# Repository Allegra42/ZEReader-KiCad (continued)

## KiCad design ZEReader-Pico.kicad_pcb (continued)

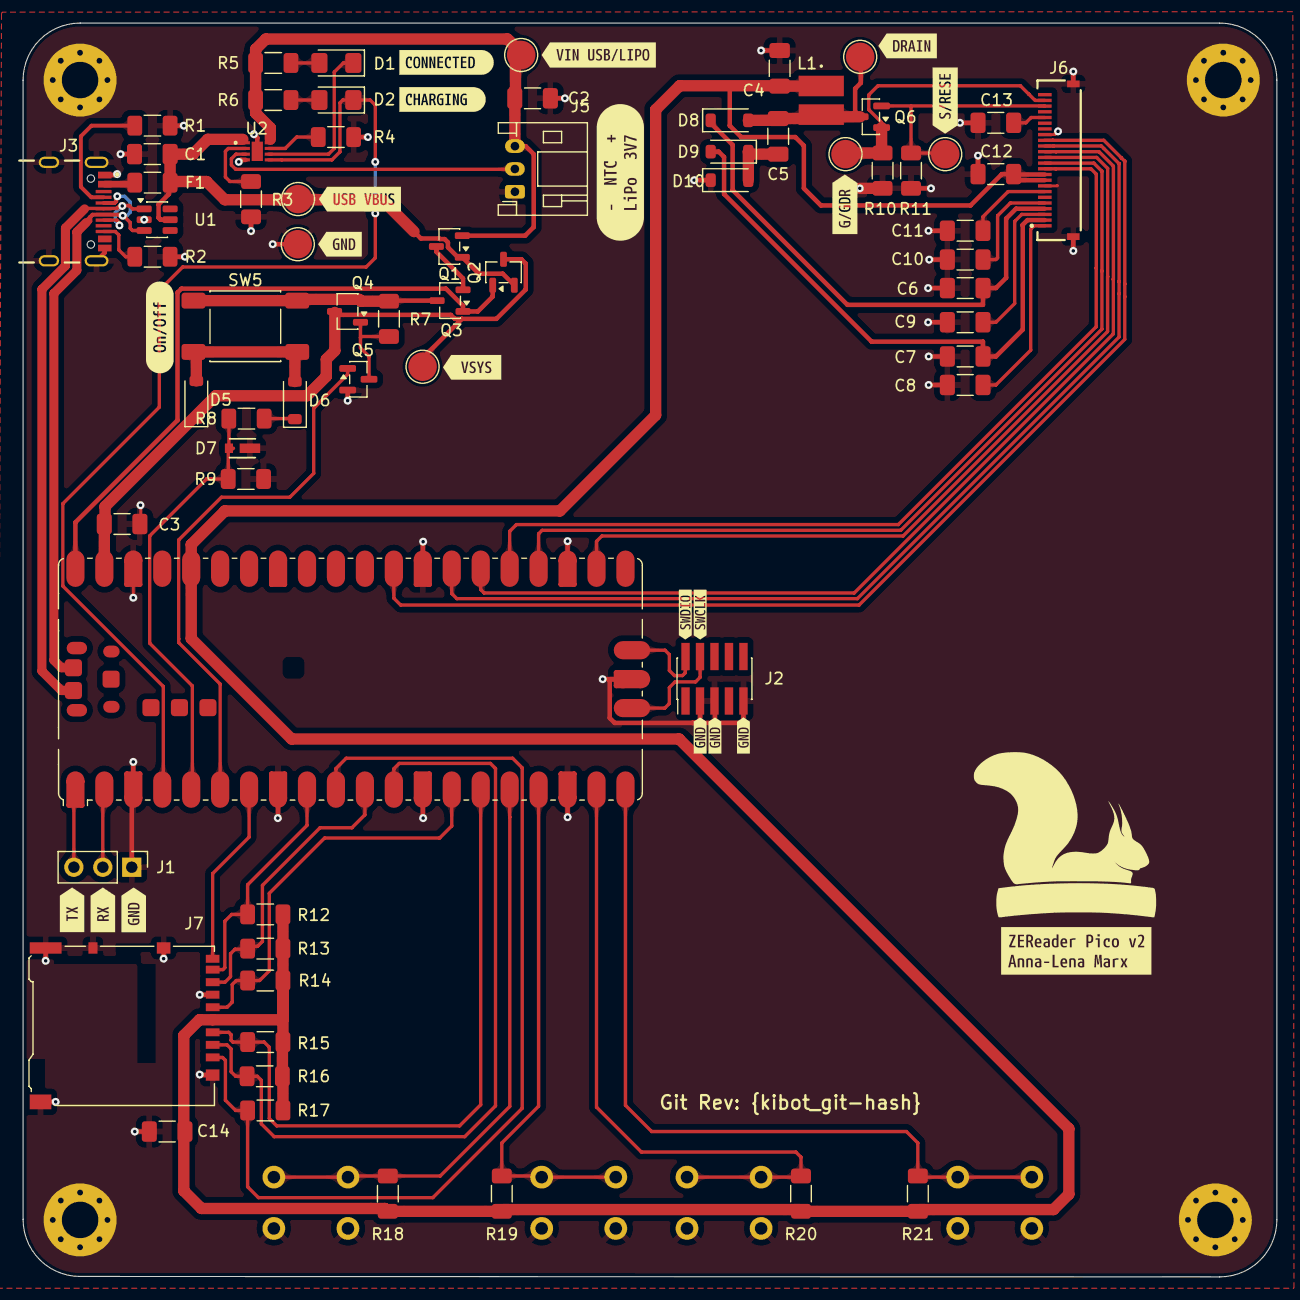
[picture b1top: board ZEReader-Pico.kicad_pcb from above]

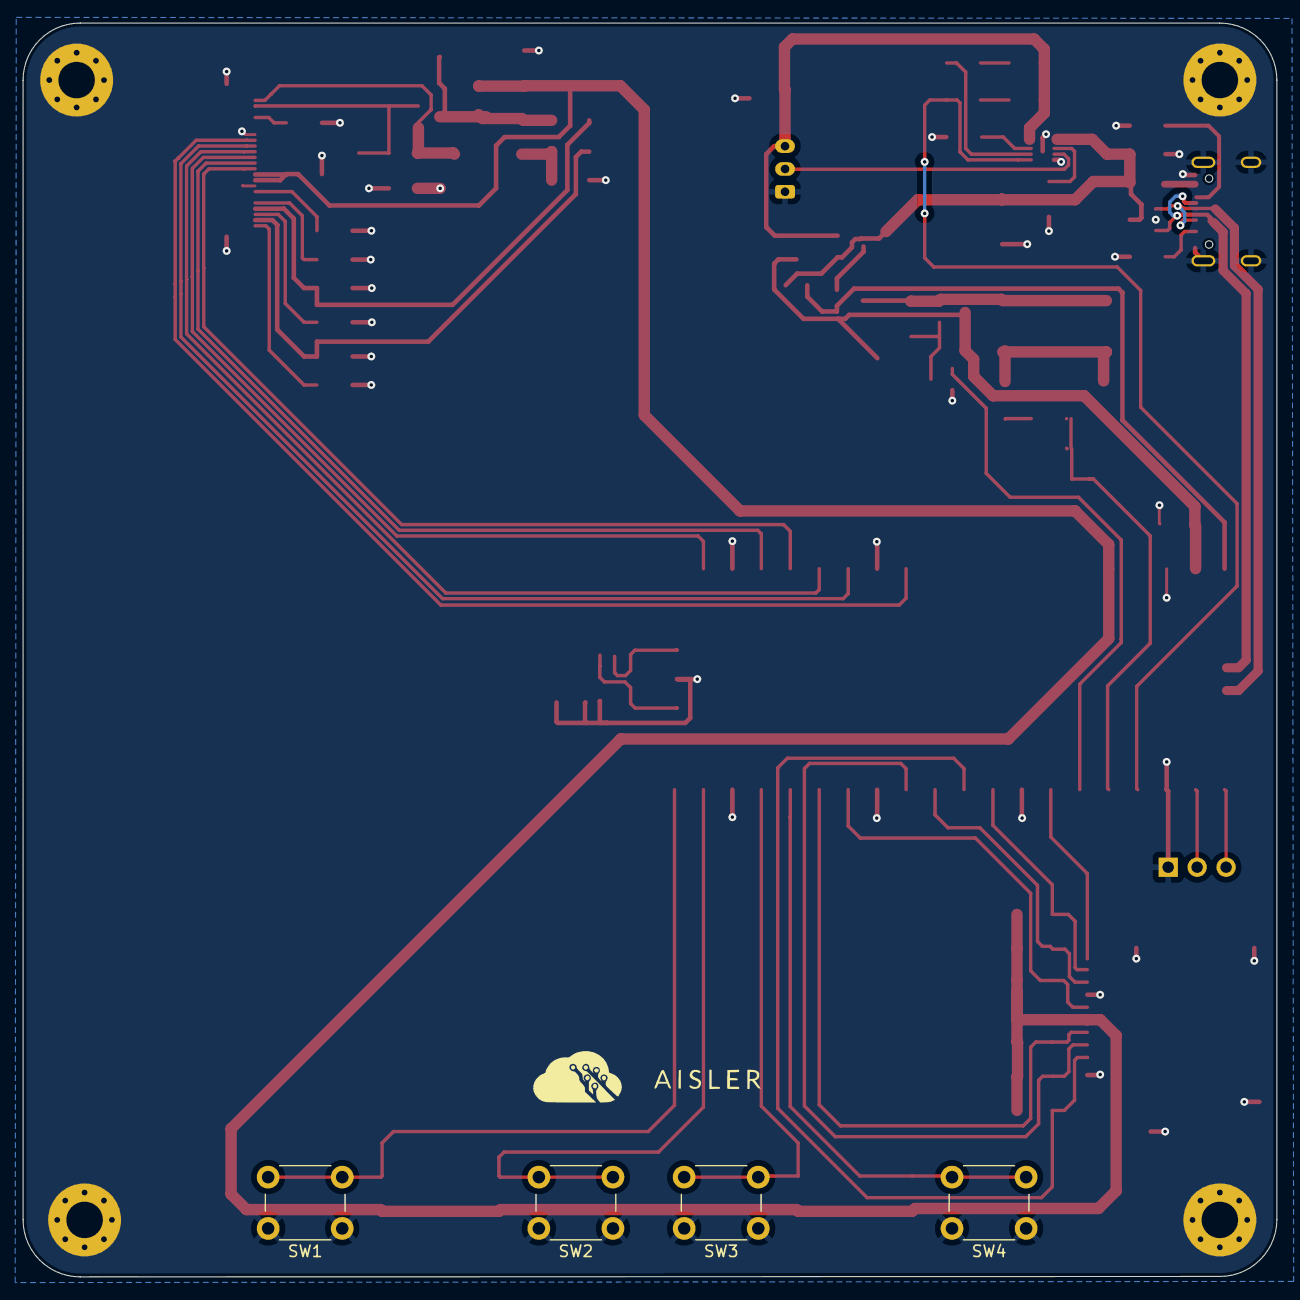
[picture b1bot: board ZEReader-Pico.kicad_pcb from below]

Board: 2 copper layers, 110.0 x 110.0 mm, 96 parts (4 on the bottom side), 57 nets.

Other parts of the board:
kibuzzard-1: G***; kibuzzard-6910EAB5
kibuzzard-2: G***; kibuzzard-6910F1E0
kibuzzard-3: G***; kibuzzard-6910EA92
kibuzzard-4: G***; kibuzzard-6910F073
kibuzzard-5: G***; kibuzzard-6910F03B
kibuzzard-6: G***; kibuzzard-6910EACE
kibuzzard-7: G***; kibuzzard-6910EA89
kibuzzard-8: G***; kibuzzard-6910EAAC
kibuzzard-10: G***; kibuzzard-6910EB09
kibuzzard-14: G***; kibuzzard-6910EC15
kibuzzard-15: G***; kibuzzard-6910EC3B
kibuzzard-16: G***; kibuzzard-6910EC48
kibuzzard-17: G***; kibuzzard-6910ECBF
kibuzzard-691E57BD: G***; kibuzzard-691E57BD
kibuzzard-691E5833: G***; kibuzzard-691E5833
kibuzzard-691EE38D: G***; kibuzzard-691EE38D
kibuzzard-691EE385: G***; kibuzzard-691EE385
kibuzzard-691EE480: G***; kibuzzard-691EE480
kibuzzard-691EE489: G***; kibuzzard-691EE489
kibuzzard-691EE495: G***; kibuzzard-691EE495

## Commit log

2025-01-26 Create inital KiCad hierarchical schematics structure
2025-01-27 Adds SD card connector, control buttons and debug headers
2025-01-27 Add EPD Driver Circuit
2025-01-29 Added USB-C, Battery Charging andOn/Off
2025-01-30 Added some more notes, testpoints and rechecked footprints and parts
2025-01-31 Changed buttons to smaller ones, updated some comments
2025-02-03 Added CC line pulldown resistors
2025-02-03 Starting with KiBot CI
2025-02-03 trigger KiBot test
2025-02-03 fix always() in github actions
2025-02-03 fix upload action, add manual trigger
2025-02-03 Fix workflow
2025-02-03 Own KiBot config
2025-02-03 Proper KiBot variables
2025-02-03 Defined root schematic file
2025-02-03 fix missing :
2025-02-03 fix: commented out not used filters section
2025-02-04 Add 3rd party symbols, footprints and 3d models to make the repo self-contained
2025-02-04 issue in kibot config
2025-02-04 fix selfcontained and kibot output
2025-02-04 switched to self-contained symbols, update kibot conf
2025-02-04 fix selfcontainment issues, added 2D rendering
2025-02-04 selfcontaining, KiBot output
2025-02-04 fix typo
2025-02-04 selfcontainment, smaller fixes
2025-02-04 selfcontainment fixes
2025-02-04 Imported Aisler design rules, routed power and display booster
2025-02-04 Added readme
2025-02-05 Initial routing finished
2025-02-05 Changed USB connector due to manufacturing rule violations
2025-02-05 fix typo in workflow
2025-02-05 Worked on Design, eliminating errors
2025-02-07 updated KiBot tasks
2025-02-07 Updated KiBot config for manufacturing
2025-02-07 fix: manufacturing output
2025-02-07 fix: naming
2025-02-07 fix: corrected button/connector location
2025-02-07 try alternate display connector
2025-02-10 Reordered and rerouted display charge pump part
2025-02-10 Redesigned SD Reader and Buttons
2025-02-11 Rerouted whole PCB
2025-02-11 Also generate a PCB Design pdf
2025-02-11 try to fix pcb sheet export
2025-02-11 hopefully generate the expected PCB output
2025-02-11 Fix some parts of PCB sheet generation
2025-02-11 Remove unneeded layers from PCB design output
2025-02-11 trying different mask colors
2025-02-11 fix pcb sheet generation
2025-02-11 moved display booster part down do get some space on the upper edge
2025-02-11 Changed USB-C connector due to availability issues
2025-02-12 cleanup silkscreen and alignments
2025-02-12 Added license and pointer to Aisler
2025-02-12 Move display connector, give the flex cable more slack
2025-02-12 Small Silkscreen updates
2025-02-12 Rerouted two parts
2025-02-12 Optimized track lengths
2025-02-12 Add kicad_pcb to CI outputs
2025-02-12 Fix kibot config
2025-02-12 Fix Fab output generation
2025-02-12 Use sed for variable replacement
2025-03-07 fix: Adds ToDos for issues in the current design
2025-06-06 updated some values after testing out tuning details
2025-07-23 some cleanup, added pictures
2025-07-23 doc: add PCB rendering in readme
2025-08-17 Migrate to KiCad 9, start working on the new revision
2025-08-19 reworked epaper-driver schematic - corrected inverted ffc adapter
2025-08-19 switch to KiCad Pico extended symbol
2025-08-19 fully connect the sd connector, redraw sd and buttons
2025-08-20 updated power path, connect USB-C to pico's USB data
2025-09-05 v2: major changes
    - Move to hierarchical labels
    - use another RP Pico Footprint
    - split power path in USB/charging and on/off with a button approach in order to control turning on and off
    with the RP Pico, make use of long presses and delay turning of the voltage in order to do a proper shutdown
    - introduce another charging controller with a better performance an a lower voltage needed in order to charge the battery
    - rework display booster circuit
2025-09-25 Worked on power on/off button, epaper driver and board/routing
2025-10-24 v2: finished schematics, start routing
    The schematics for v2 should be mostly finished by now.
    The new on/off button is ready and tested with a breadboard setup.
    It now uses two FETs for a self-holding circuit for turning the
    device on and off. To reach a safe logic level for Pico 2, a
    2.7V Zener diode is used together with a pull-down for E9 affected
    RP2350 revisions.
2025-11-01 First routing approach for v2
2025-11-02 Update routing and Kibot version
2025-11-07 Reworked v2 routing
    - some general improvements
    - reworked component numbering
    - routed and tuned differential pair (USB)
    - added stiching vias and improved ground fills
2025-11-07 some minor improvements after evaluating the CI run
2025-11-07 reapplied the KiCad Logo
2025-11-09 v2: final touch
    - add proper ESD diodes for USB
    - move the USB fuse right after the connector
    - pretty labels for test points
2025-11-09 mirrored front side logo
2025-11-09 better integration for the USB ESD diodes, better trace length matching
2025-11-14 fix two labeling issues
2025-11-18 Connect both USB data lines again, checked everything with datasheets again
2025-11-18 rewrite the project's readme and update it for rev2
2025-11-19 Updated zener diode footprint
2025-11-20 Reworked the PCB after review
2025-11-21 Bigger Zener, improved BoM, general improvements
2025-11-21 Removed unneeded paste under Pi Pico, updated KiBot BoM generation
2025-11-21 Add missing git rev variable in one schematic file, updated BOM generation
2025-11-21 update KiBot config
2025-11-30 Add proper charging detection, fix zener footprint
    Connect the BQ25 status pin to the microcontroller for a proper
    charging detection (low active).
    Correct the footprint for the selected zener diode.
    Somehow, the wrong footprint got assigned.
2025-12-06 Avoid using the ADC pins for anything but ADC tasks
2025-12-09 Add an voltage bypass mode when USB-C is connected
    When USB-C is connected, the device should be charging, but also powered,
    without taking care of the on/off button's state.
    Otherwise, flashing the device via USB-C would only be
    possible as long as the button is pressed which makes the usage
    experience a mess and flaky.
    This uses p-MOSFETs to do the switch and
2025-12-12 Introduce KiCad native Jobsets as an alternative to KiBot
    Adds KiCad a jobset together with a new GitHub workflow file
    to generate the project outputs without external tooling.
    Some general work on the USB-Powerpath routing.
2026-02-01 Add known issues for the ZEReader V2 PCB
    The ZEReader V2 PCB is manufactured and tested since 12/2025,
    so it was about time to add known issues for this version.
